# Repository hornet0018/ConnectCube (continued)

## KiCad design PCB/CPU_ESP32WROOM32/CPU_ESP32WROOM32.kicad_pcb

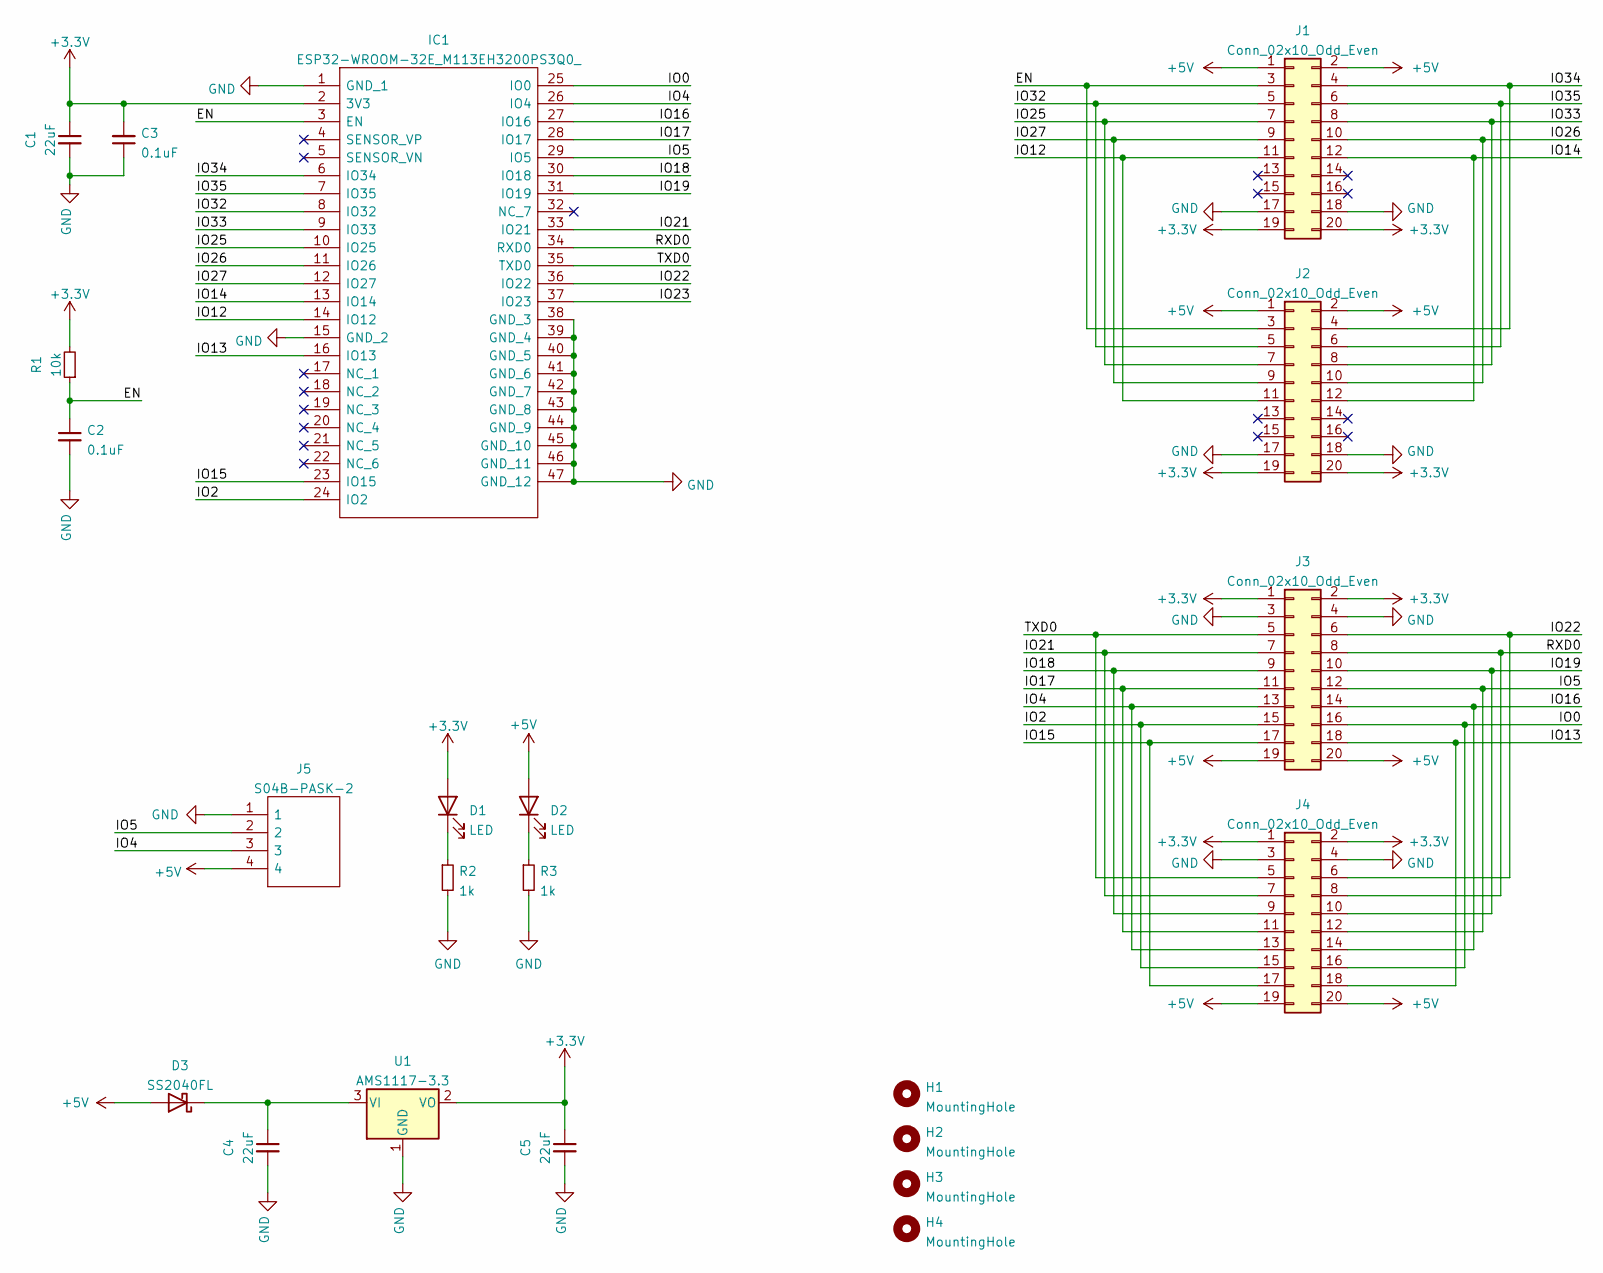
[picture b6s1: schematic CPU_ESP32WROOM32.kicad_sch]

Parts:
C1, C4, C5: 22uF; C_0603_1608Metric_Pad1.08x0.95mm_HandSolder
C2, C3: 0.1uF; C_0603_1608Metric_Pad1.08x0.95mm_HandSolder
D1, D2: LED; LED_0603_1608Metric_Pad1.05x0.95mm_HandSolder
D3: SS2040FL; D_SOD-123F
H1, H2, H3, H4: MountingHole; MountingHole_3.2mm_M3_Pad_Via
IC1: ESP32-WROOM-32E_M113EH3200PS3Q0_; ESP32WROOM32EM113EH3200PS3Q0; Manufacturer_Part_Number ESP32-WROOM-32E(M113EH3200PS3Q0); Mouser Part Number 356-ESP32WRM320EH3PS
J1, J3: Conn_02x10_Odd_Even; PinSocket_2x10_P2.54mm_Vertical_SMD
J2, J4: Conn_02x10_Odd_Even; PinHeader_2x10_P2.54mm_Vertical_SMD
J5: S04B-PASK-2; S04BPASK2; Manufacturer_Part_Number S04B-PASK-2
R1: 10k; R_0603_1608Metric_Pad0.98x0.95mm_HandSolder
R2, R3: 1k; R_0603_1608Metric_Pad0.98x0.95mm_HandSolder
U1: AMS1117-3.3; SOT-223-3_TabPin2

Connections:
+3V3: C1.1, C3.2, C5.1, D1.2 (A), IC1.2 (3V3), J1.19, J1.20, J2.19, J2.20, J3.1, J3.2, J4.1, J4.2, R1.2, U1.2 (VO)
+5V: D2.2 (A), D3.2 (A), J1.1, J1.2, J2.1, J2.2, J3.19, J3.20, J4.19, J4.20, J5.4
/EN: C2.1, IC1.3 (EN), J1.3, J2.3, R1.1
/IO0: IC1.25 (IO0), J3.16, J4.16
/IO2: IC1.24 (IO2), J3.15, J4.15
/IO4: IC1.26 (IO4), J3.13, J4.13, J5.3
/IO5: IC1.29 (IO5), J3.12, J4.12, J5.2
/IO12: IC1.14 (IO12), J1.11, J2.11
/IO13: IC1.16 (IO13), J3.18, J4.18
/IO14: IC1.13 (IO14), J1.12, J2.12
/IO15: IC1.23 (IO15), J3.17, J4.17
/IO16: IC1.27 (IO16), J3.14, J4.14
/IO17: IC1.28 (IO17), J3.11, J4.11
/IO18: IC1.30 (IO18), J3.9, J4.9
/IO19: IC1.31 (IO19), J3.10, J4.10
/IO21: IC1.33 (IO21), J3.7, J4.7
/IO22: IC1.36 (IO22), J3.6, J4.6
/IO23: IC1.37 (IO23)
/IO25: IC1.10 (IO25), J1.7, J2.7
/IO26: IC1.11 (IO26), J1.10, J2.10
/IO27: IC1.12 (IO27), J1.9, J2.9
/IO32: IC1.8 (IO32), J1.5, J2.5
/IO33: IC1.9 (IO33), J1.8, J2.8
/IO34: IC1.6 (IO34), J1.4, J2.4
/IO35: IC1.7 (IO35), J1.6, J2.6
/RXD0: IC1.34 (RXD0), J3.8, J4.8
/TXD0: IC1.35 (TXD0), J3.5, J4.5
GND: C1.2, C2.2, C3.1, C4.2, C5.2, IC1.1 (GND_1), IC1.15 (GND_2), IC1.38 (GND_3), IC1.39 (GND_4), IC1.40 (GND_5), IC1.41 (GND_6), IC1.42 (GND_7), IC1.43 (GND_8), IC1.44 (GND_9), IC1.45 (GND_10), IC1.46 (GND_11), IC1.47 (GND_12), J1.17, J1.18, J2.17, J2.18, J3.3, J3.4, J4.3, J4.4, J5.1, R2.2, R3.2, U1.1 (GND)
unnamed: C4.1, D3.1 (K), U1.3 (VI)
unnamed: D1.1 (K), R2.1
unnamed: D2.1 (K), R3.1

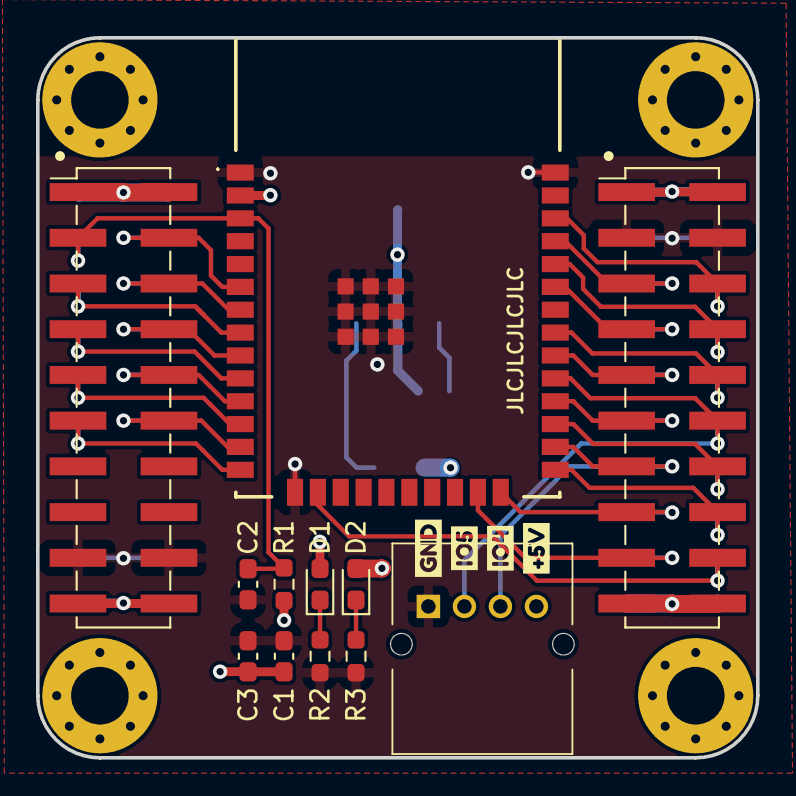
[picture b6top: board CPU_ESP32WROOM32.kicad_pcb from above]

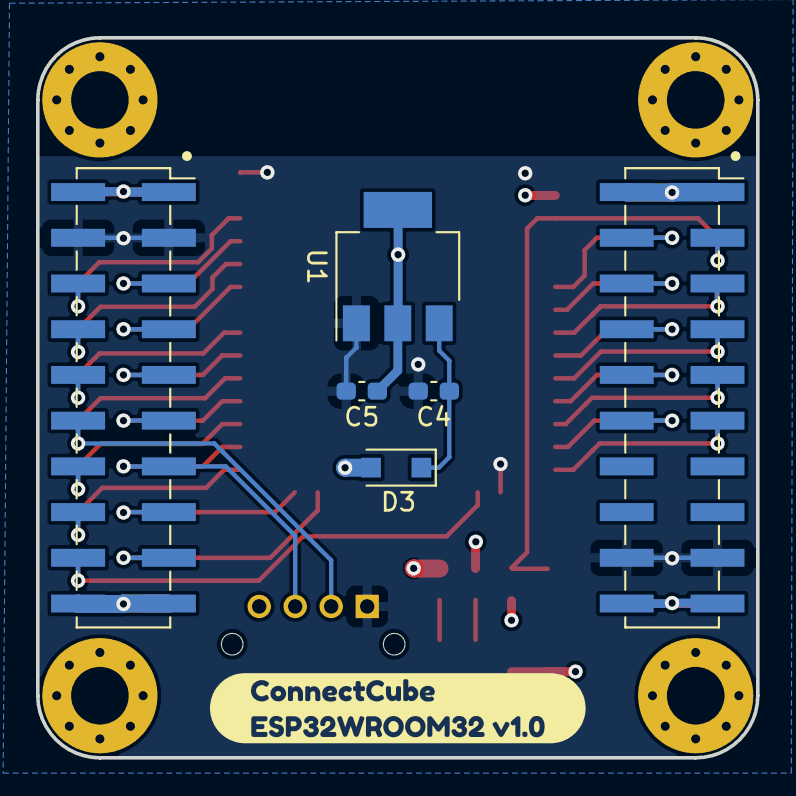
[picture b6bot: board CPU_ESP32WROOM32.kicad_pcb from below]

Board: 6 copper layers, 40.0 x 40.0 mm, 27 parts (7 on the bottom side), 30 nets.

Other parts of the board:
kibuzzard-63EB5F48: G***; kibuzzard-63EB5F48
kibuzzard-63EB5F50: G***; kibuzzard-63EB5F50
kibuzzard-63EB5F59: G***; kibuzzard-63EB5F59
kibuzzard-63EB5F61: G***; kibuzzard-63EB5F61
kibuzzard-63EB83FE: G***; kibuzzard-63EB83FE

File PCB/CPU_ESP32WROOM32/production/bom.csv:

Designator,Footprint,Quantity,Value,LCSC Part #
"C1, C4, C5",C_0603_1608Metric_Pad1.08x0.95mm_HandSolder,3,22uF,
"C2, C3",C_0603_1608Metric_Pad1.08x0.95mm_HandSolder,2,0.1uF,
"D1, D2",LED_0603_1608Metric_Pad1.05x0.95mm_HandSolder,2,LED,
D3,D_SOD-123F,1,SS2040FL,
"H1, H2, H3, H4",MountingHole_3.2mm_M3_Pad_Via,4,MountingHole,
IC1,ESP32WROOM32EM113EH3200PS3Q0,1,ESP32-WROOM-32E_M113EH3200PS3Q0_,
"J1, J3",PinSocket_2x10_P2.54mm_Vertical_SMD,2,Conn_02x10_Odd_Even,
"J2, J4",PinHeader_2x10_P2.54mm_Vertical_SMD,2,Conn_02x10_Odd_Even,
J5,S04BPASK2,1,S04B-PASK-2,
R1,R_0603_1608Metric_Pad0.98x0.95mm_HandSolder,1,10k,
"R2, R3",R_0603_1608Metric_Pad0.98x0.95mm_HandSolder,2,1k,
U1,SOT-223-3_TabPin2,1,AMS1117-3.3,

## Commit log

2023-02-27 v1.0
2023-03-03 add sample
2023-03-04 ADD 0.96LCD
2023-03-04 動作確認
2023-03-17 LCD_0.96_v1.0
2023-03-18 LCD_0.96_v1.1
2023-03-19 IO_TESTER_v1.0
2023-04-05 add_base_unit_2x2_v1.0
2023-04-23 PROGRAMER UNIT v1.0
2023-04-23 arduino-cloud-demo
2023-04-23 lovyangfx-demo
